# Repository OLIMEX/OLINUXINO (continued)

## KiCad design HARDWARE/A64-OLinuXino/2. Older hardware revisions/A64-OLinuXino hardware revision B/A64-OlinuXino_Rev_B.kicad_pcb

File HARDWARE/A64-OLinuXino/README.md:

## Information about the hardware schematics, design sources, and revision changes

PDF exports of the schematics are found in this folder. Deisgn files are found in the folders, each folder features all required files for a specific hardware revision as indicated by the folder name. To access the design files you need the latest beta version of KiCAD. Using the latest stable version usually will NOT suffice.

The initial release of A64-OLinuXino boards was revision C. The six variants of the board so far are:

* A64-OLinuXino-1G with 1GB RAM but NO flash and NO WiFi/BLE connectivity

* A64-OLinuXino-1Ge16GW with 1GB RAM and 16GB extra eMMC flash and extra WiFi/BLE module

* A64-OLinuXino-1Ge16GW-EA with 1GB RAM and 16GB extra eMMC flash and extra WiFi/BLE module + external antenna

* A64-OLinuXino-1Ge4GW with 1GB RAM and 4GB extra eMMC flash and extra WiFi/BLE module

* A64-OLinuXino-1Gs16M with 1GB RAM, no NAND or eMMC flash, no WiFi/BLE, extra 16MB SPI flash

* A64-OLinuXino-2Ge8G-IND with 2GB RAM and 8GB extra flash but NO WiFi/BLE connectivity; with components that work in the industrial -40+85C temperature range

### Hardware revision changes log:

#### Hardware revision C

* initial release

#### Hardware revision D

* 1. Adjusted white print of label C184.
* 2. Added bypass R66 NA(0R) near FET2.
* 3. Added white print for the UART connector at the bottom of the board (Tx,Rx,GND).
* 4. Fixed white print of R106 and R116 (labels were swapped)
* 5. R29 placed a bit further from C84
* 6. 1.5v test pad name was changed to "DDR-VCC" because the RAM memory can work at 1.3V.
* 7. Names of the jumpers lineinr/micin1p1 and lineinl/micin1n1 were changed to lineinr/micin1 and lineinl/micin2.
* 8. The jumper phoneoutr(l)/lineootr(l) was renamed to hphoneoutr(l)/lineoutr(l).

#### Hardware revision E

* 1. Changed the eMMC from eMMC (4GB,1.00mm pitch) to eMMC (16GB,0.50mm pitch). Some of the surrounding components changed too.
** 1.1 Removed RM1(RA1206_(4X0603)_4B8_10k), RM2(RA0805_(4X0402)_22R), RM3(RA0805_(4X0402)_22R), RM4(RA1206_(4X0603)_4B8_10k), RM5(RA0805_(4X0402)_22R)
* 2. C212 and C213 were changed from 27pF to 33pF and from 0603 to 0402 as component optimisation.
* 3. R66 value changed from NA(0R) to NA(22R)
* 4. RM15's package changed from RA1206_(4X0603)_4B8_22R to RA0805_(4X0402)_22R as component optimisation.
* 5. C119 and VR1 changed from PTH to SMT type in the KiCad settings. In reallity, C119 and VR1 did not change. 
* 6. PWRLED1 and CHGLED1 labels corrected in the white print.
* 7. WP_Enable1 jumper added to the SPI_Flash.
* 8. U4 changed from NA(H27UBG8T2BTR-BC(TSOP48)) to NA(MT29F64G08CBABA-WP(TSOP48)), i.e. when populated 8GB NAND instead of 4GB.
* 9. MICRO_SD(TFC-WPAPR-08) package change - corrected cream layer and origin.
* 10. PWR_PC1 jumper state changed to Soldered(2-3); Opened(1-2) so that 1.8V wire is connected to the eMMC by default.
* 11. Serial resistors added to the Ethernet PHY's Tx lines for better EMI supression and RLC filters to the clock lines.
* 12. C198 connected to the right side of the RGMII_RXCLK line.
* 13. The Wi-Fi's baloun now matched with the same "Pi" - filter like in Teres-I, so:
	C105 changed from 33pF to 10pF
	C106 changed from NA to 0.8pF
	R62 was exchanged with inductor 3.3nH
	C107 was changed from NA to 1.5pF
* 14. The WiFi's antenna mirrored

#### Hardware revision E1

* 1. eMMC KLMAG2GEND-B031(FBGA153)(16G) changed with new eMMC KLMAG1JETD-B041(FBGA153)(16G)

#### Hardware revision F

* 1. Added R62(10k/0402) pull-down to the eMMC's data strobe line;
* 2. RM14, RA0805_(4X0402)_22R replaced by 4 resistors 22R/0402, i.e. R121-R124; R121 was placed away from UEXT for to make shorter eMMC's data strobe line length;
* 3. R73[NA(22R/0402)] was added to enable SPI0 software CS option to the UEXT via PH10, when the SPI_Flash is populated. By defalut, it will reamin as it was, i.e. R124(22R/0402) populated!, while R73(NA)!;
* 4. L9 was changed from 2.7nH/L0402 to NA(2.7nH/L0402), and C88 from 24pF to NA(24pF);
* 5. MIPI-DSI1 changed: MIPI-DSI1 connector's pinout completely changed for Raspberry-Pi compatability; added the resistors: R125 to R132;
* 6. In the DRC drill to drill clerance was set to 12mils and all related errors were corrected;
* 7. UEXT1 was changed from NA(HN2x5) to HN2x5;
* 8. All 3Ds were assigned;
* 9. It was added C94(NA/0402) to the eMMC's clock line just in case;
* 10. NAND and related components removed forever;
* 11. In the schematic all "/" signs were exchanged with "\";
* 12. Improvements around the placement of a number of resistors related to the PHY signals to reduce EMI emissions;
* 13. Added U4 EEPROM - AT24C16C-SSHM-T(SOIC-8_150mil) and also C39, 100nF/10V/10% to the UEXT's I2C to avoid conflict with the same EEPROM on the LCD-Driver board. It is placed by default;
* 14. R15[NA(22R/R0402)] added in serial to the eMMC's datastrobe signal to be able to disconnect when no HS400 mode or to add a serial filter to reduce EMI;
* 15. UBOOT1, PWRON1 and RESET1 packages changed from OLIMEX_Buttons-FP:uTACTIL to OLIMEX_Buttons-FP:IT1185AU2_V2;
* 16. U2 and U3's packages improved;
* 17. LAN1's package improved;
* 18. D1 moved a little bit away from the PWR-JACK's + pad;
* 19. Q2 package changed from Q32.768kHz\12.5pF/20ppm/4P/SMD8038 to Q32.768kHz/12.5pF/2P/SMD1206;
* 20. L7 package changed from 2.7nH\L0402 to NA(2.7nH\L0402), and C198 changed from 24pF to NA(24pF);
* 21. R100 changed from 22R/0402 to FB1, FB0402/PZ1005U601-R45TF-1;
* 22. R69 changed from 22R/0402 to FB2, FB0402/PZ1005U601-R45TF-1;
* 23. The GND polygons in the top and bottom opened to allow for metal cover soldering.

#### Hardware revision G

* 1. Added antenna ANT2(NA(U.FL-R-SMT-1)), R16(0R) and R17(NA/0R);
* 2. Removed FB1(FB0402/PZ1005U601-R45TF-1) and FB2(FB0402/PZ1005U601-R45TF-1) and placed R18(22R/0402) and R19(22R/0402) resistors instead. Using FB1 and FB2 was meant to improve the EMI, but it yielded no results;
* 3. Adjusted the lengths of some eMMC wires;
* 4. C93 changed from 24pF to 24pF\50V/5%. C88 and C198 changed from NA/24pF to NA(24pF\50V/5%);
* 5. Changing 5.1 eMMC at 3.3V (up from 1.8V operation) for better reliability, PWR_PC1 jumper has to be set to position 1-2 for 3.3V operation.

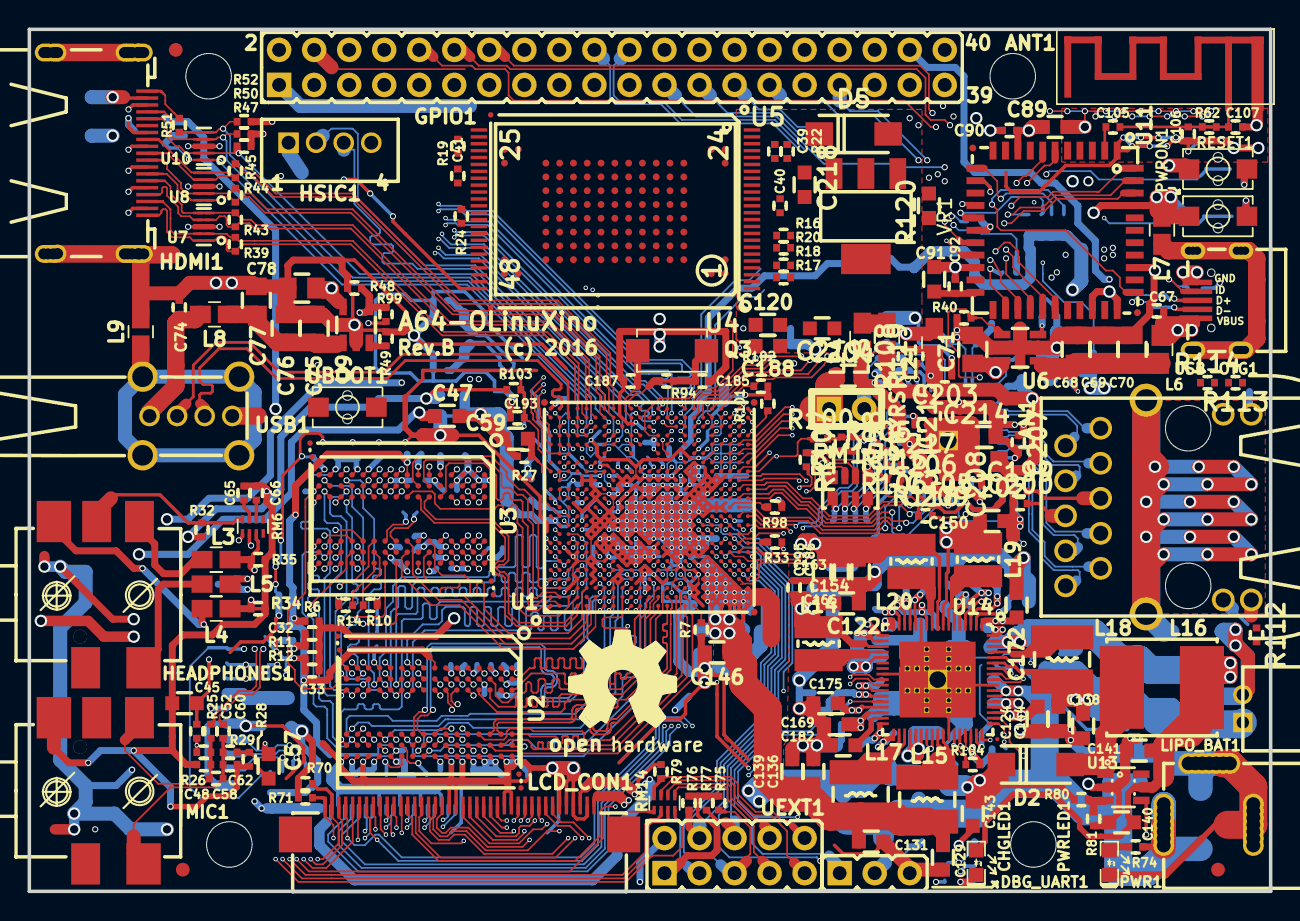
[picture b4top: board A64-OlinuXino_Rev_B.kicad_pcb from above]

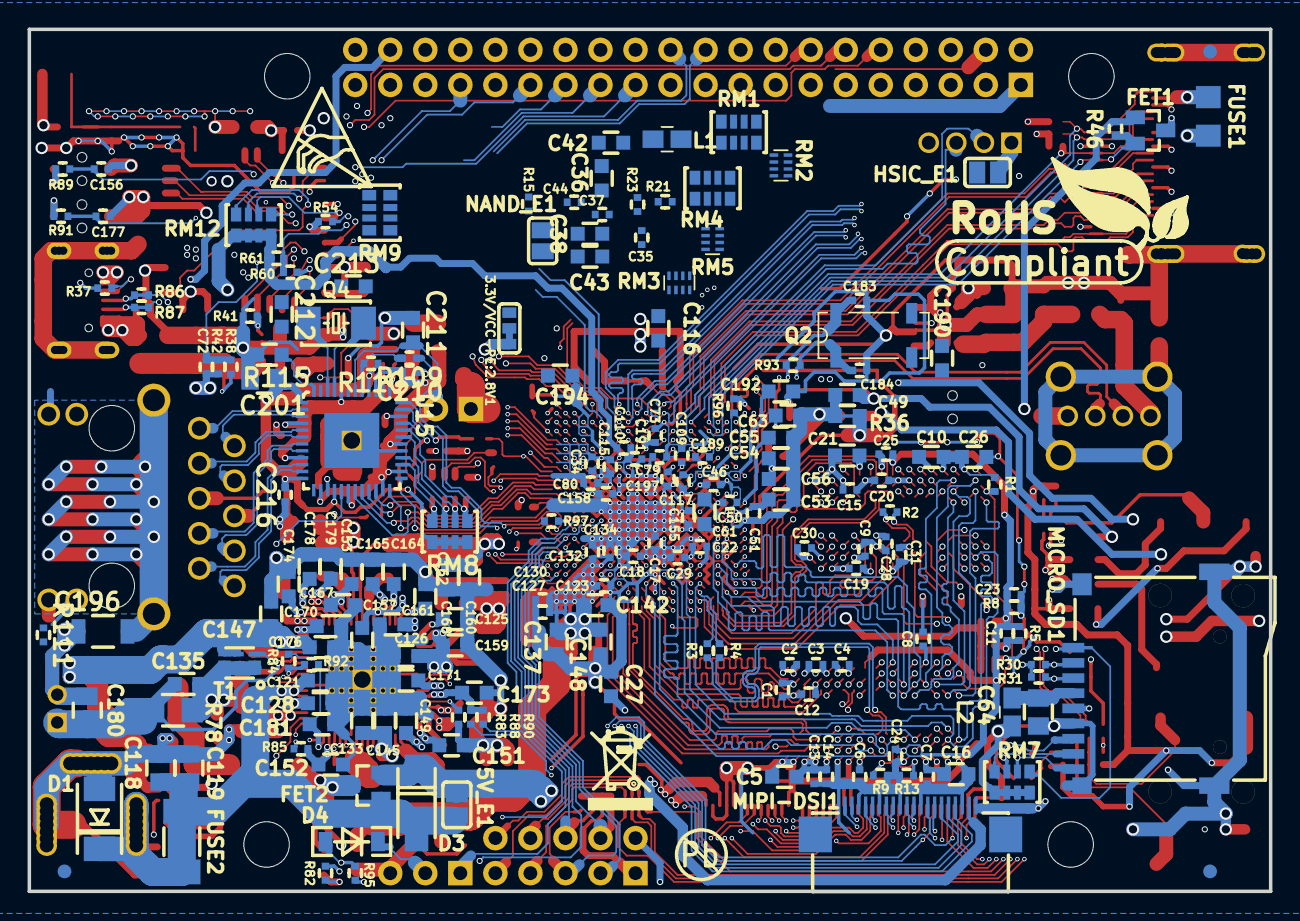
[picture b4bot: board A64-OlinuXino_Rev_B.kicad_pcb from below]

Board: 6 copper layers, 90.0 x 62.5 mm, 388 parts (188 on the bottom side), 393 nets.

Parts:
3.3V/VCC-PE:2.8V1: Opened(2-3);Closed(1-2); SJ_2_SMALL_12_TIED
5V_E1: Opened; SJ
ANT1: PCB_WIFI_ANT; bt_antenna_1ant_2gnd
C1, C2, C3, C4, C6, C7, C8, C9, C11, C12, C13, C14, C15, C17, C18, C19, C20, C22, C23, C24, C25, C28, C29, C30, C31, C32, C33, C34, C35, C37, C44, C46, C50, C51, C52, C60, C65, C66, C67, C72, C73, C74, C79, C80, C90, C92, C109, C110, C115, C117, C123, C127, C130, C132, C134, C155, C156, C158, C177, C186, C189, C191, C195, C197, C199, C200, C203, C206, C207, C208, C209, C210, C215, C216, C217: 100nF; C_0402_5MIL_DWS
C5, C10, C16, C21, C26, C42, C47, C49, C53, C54, C57, C59, C63, C89, C91, C116, C121, C122, C124, C125, C126, C128, C129, C131, C133, C136, C138, C139, C140, C141, C143, C144, C145, C146, C147, C148, C149, C150, C151, C152, C153, C154, C157, C159, C161, C162, C164, C165, C166, C167, C168, C169, C170, C171, C172, C173, C175, C176, C178, C179, C188, C192, C194: 10uF/6.3V/0603; C_0603_5MIL_DWS
C27, C36, C38, C43, C45, C55, C120, C135, C137, C142, C160, C163, C181, C182, C190: 1uF/6.3V/0603; C_0603_5MIL_DWS
C39, C40, C41: NA(100nF); C_0402_5MIL_DWS
C48, C62, C105, C185, C187: 33pF; C_0402_5MIL_DWS
C56, C61: 2.2uF/6.3V/0603; C_0603_5MIL_DWS
C58: 100pF; C_0402_5MIL_DWS
C64, C68, C69, C70, C71, C75, C76, C77, C78, C118, C119, C180, C201, C202: 47uF/6.3V/0805; C_0805_5MIL_DWS
C106, C107, C198: NA; C_0402_5MIL_DWS
C174: NA(10uF/6.3V/0603); C_0603_5MIL_DWS
C183, C184: 10pF; C_0402_5MIL_DWS
C193: NA(1nF); C_0402_5MIL_DWS
C196: 1nF/2kV/X7R/1206; C_1206_5MIL_DWS_ISO
C204, C205, C214, C218, C219: 22uF/6.3V; C_0603_5MIL_DWS
C211: NA(10uF/6.3V); C_0603_5MIL_DWS
C212, C213: 27pF; C_0603_5MIL_DWS
CHGLED1: LED/YELLOW/0603; LED_0603_KA
D1: SMBJ6.0A; DO214AA
D2, D3: 1N5822/SS34/SMA; SMA-KA
D4: 1N5819(S4SOD-123); SOD-123_1C-2A_KA
D5: 1N4007/SMA; SMA-KA
DBG_UART1: NA(HN1x3); HN1x3
FET1: BSS138(SOT23-3); SOT23
FET2: IRLML6402(SOT-23); SOT23
FUSE1: FSMD035; FUSE-1206
FUSE2: NA(5025); FUSE-5025
GPIO1: NA(HN2x20); HN2x20
HDMI1: HDMI-SWM-19
HEADPHONES1: SCJ325P00XG0B02G
HSIC1: B4B-PH-K-S
HSIC_E1: Opened; SJ
L1, L2, L3, L4, L5, L6, L7, L8, L9, L21, L23, L24: FB0805/600R/2A; L_0805_5MIL_DWS
L14, L19, L20: SWPA3015S1R5NT(1.5uH/2.30A/DCR<0.1R/CD32); CD32
L15, L17, L18: SWPA4018S1R5NT(1.5uH/3.35A/DCR<0.1R/CD43); CD42(43)
L16: 2.2uH/3A/YS75/7x8; YS75_7X8MM
LAN1: TM211Q01FM22
LCD_CON1: FPV-WZA21-40-LF
LIPO_BAT1: DW02R; LIPO_BAT-CON2DW02R
MIC1: SCJ325P00XG0B02G
MICRO_SD1: MICRO_SD(TFC-WPAPR-08); TFC-WPAPR-08
MIPI-DSI1: FPV-WZA21-20-LF
MountingHole: Mounting_hole_3.3mm
MountingHole#2, MountingHole#3, MountingHole#4: Mounting_hole_3.3mm
NAND_E1: Unsoldered; SJ
PHYRST1: HN1x2(Opened); HN1x2_Jumper
PWR1: PWRJ-2mm(YDJ-1136); PWR_JACK_UNI_MILLING
PWRLED1: LED/Red/0603; LED_0603_KA
PWRON1: IT1185AU2; uTACTIL
Q2: MC-306_32.768KHZ/SMD_8038/6pF; MC306-HS
Q3: 4SB24.000F20E15/5x3.2mm/20ppm/20pF; Q5x3.25
Q4: E4SB25.000F20E15(25MHz/20pF/20ppm/5x3.2mm); HCX-4S_2Pins_5.0x3.2mm
R1, R5, R8, R11, R12: 2k/1%; R_0402_5MIL_DWS
R2: 100R/1%; R_0402_5MIL_DWS
R3, R4, R33, R54, R100, R105, R109: 22R; R_0402_5MIL_DWS
R6, R19, R20, R24, R84, R96, R97, R98, R116, R118: NA; R_0402_5MIL_DWS
R7, R9, R10: 243R/1%; R_0402_5MIL_DWS
R13, R14: NA(243R/1%); R_0402_5MIL_DWS
R15, R16, R17, R22, R48, R61, R104: NA(10k); R_0402_5MIL_DWS
R18: NA(22R); R_0402_5MIL_DWS
R21, R23, R31, R37, R40, R42, R52, R76, R79, R83, R85, R95, R99, R106, R119: 10k; R_0402_5MIL_DWS
R25, R28, R89, R91, R92, R107, R108, R110, R111, R112, R113, R114, R117: 1k; R_0402_5MIL_DWS
R26, R29: 1.5k; R_0402_5MIL_DWS
R27: 200k/1%; R_0402_5MIL_DWS
R30, R35: 100k; R_0402_5MIL_DWS
R32: NA(1M); R_0402_5MIL_DWS
R34, R62, R86, R87, R94: 0R(Board_Mounted); R_0402_5MIL_0R(Board_Mounted)
R36: 0R(Board_Mounted); R_0603_5MIL_0R(Board_Mounted)
R38, R51: 4.7k; R_0402_5MIL_DWS
R39, R43, R44, R45: NA(510R); R_0402_5MIL_DWS
R41: 13k/1%; R_0402_5MIL_DWS
R46: 27k; R_0402_5MIL_DWS
R47, R50, R70, R71, R74, R75, R77, R82, R88, R90: 2.2k; R_0402_5MIL_DWS
R49: 3.92k/1%; R_0402_5MIL_DWS
R60: NA(0R); R_0402_5MIL_DWS
R78: 0.01R/1%/1206; R_1206_5MIL_DWS
R80: 8.25k/1%; R_0402_5MIL_DWS
R81: 1.1k/1%; R_0402_5MIL_DWS
R93: 10M; R_0402_5MIL_DWS
R101, R102: NA(2.2k); R_0402_5MIL_DWS
R103: NA(100k); R_0402_5MIL_DWS
R115: 12.1k/1%; R_0603_5MIL_DWS
R120: 120R; R_0603_5MIL_DWS
RESET1: IT1185AU2; uTACTIL
RM1, RM4: RA1206_(4X0603)_4B8_10k; RA1206_(4X0603)_4B8_xx
RM2, RM3, RM5, RM6, RM14: RA0805_(4X0402)_22R; RA0805_(4X0402)_xx
RM7, RM9, RM12: RA1206_(4x0603)_4B8_100k; RA1206_(4X0603)_4B8_xx
RM8: RA1206_(4x0603)_4B8_4.7k; RA1206_(4X0603)_4B8_xx
RM15: RA1206_(4x0603)_4B8_22R; RA1206_(4X0603)_4B8_xx
T1: WPM1481(DFN2X2-6L); DFN2x2-6L
U1: AllWinner-A64(FBGA396); FBGA396
U2, U3: K4B4G1646Q-HYK0(FBGA-96_256Mx16_DDR3-1600_11-11-1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; FBGA96(HYNIX_SAMSUNG_512MX16_DDR3)
U4: NA(H27UBG8T2BTR-BC(TSOP48)); TSOP48
U5: MTFC4GACAANA-4M_IT(TBGA100); TBGA100
U6, U9: SY6280AAC(SOT23-5); SOT-23-5
U7, U8, U10: NA(RCLAMP0524P(SLP2510P8)); SLP2510P8
U11: RTL8723BS(ComboModule); RL-SM02BD(RTL8723BS)
U13: MT3608(SOT23-6); SOT23-6
U14: AXP803(QFN68_8x8mm); QFN68
U15: KSZ9031RNXCC(QFN48_1DRILL(PADPITCH-0.5MM)); QFN48_1DRILL(PADPITCH-0.5MM)
UBOOT1: IT1185AU2; uTACTIL
UEXT1: NA(HN2x5); HN2x5
USB1: USB_A_VERTICAL; USB_A_VERTICAL_PTH
USB-OTG1: MICRO_USB/MISB-SWMM-5AB_LF; USB-MICRO_MISB-SWMM-5B_LF
VR1: AMS1117; SOT223

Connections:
1.1V_CPUS: C117.2, C120.2, C179.2, U1.H15, U14.5
1.1V_CPUX: C123.2, C127.2, C129.2, C130.2, C131.2, C132.2, C134.2, C136.2, C137.2, C139.2, C142.2, C146.2, C148.2, L15.2, L17.2, U1.AA1, U1.AA3, U1.AB2, U1.AC1, U1.AC2, U1.U6, U1.V2, U1.V3, U1.V4, U1.V5, U1.V6, U1.W1, U1.W3, U1.W4, U1.W5, U1.Y2, U1.Y3, U1.Y4
1.1V_SYS: C154.2, C155.2, C158.2, C160.2, C163.2, C166.2, C168.2, L20.2, U1.J12, U1.J13, U1.K14, U1.L13, U1.L14, U1.M13, U1.M14, U1.N14, U1.P14, U1.R13, U1.R14, U1.T15, U14.9
1.2V_HSIC: C178.2, C197.1, HSIC_E1.1, U1.K16, U14.3
3.0V_RTC: C152.1, C189.2, C190.2, R85.2, R104.1, U1.H16, U14.49
+1.5V: C1.1, C2.1, C3.1, C4.1, C5.1, C6.1, C7.1, C8.1, C9.1, C10.1, C11.1, C12.1, C13.1, C14.1, C15.1, C16.1, C17.1, C18.1, C19.1, C20.1, C21.1, C26.1, C27.1, C28.1, C29.1, C30.1, C31.1, C32.2, C150.2, L19.2, R1.2, R5.2, R11.2, U1.G7, U1.G8, U1.G9, U1.J8, U1.K6, U1.K7, U1.L6, U1.L7, U1.L8, U1.N7, U1.N8, U2.A1, U2.A8, U2.B2, U2.C1, U2.C9, U2.D2, U2.D9, U2.E9, U2.F1, U2.G7, U2.H2, U2.H9, U2.K2, U2.K8, U2.N1, U2.N9, U2.R1, U2.R9, U3.A1, U3.A8, U3.B2, U3.C1, U3.C9, U3.D2, U3.D9, U3.E9, U3.F1, U3.G7, U3.H2, U3.H9, U3.K2, U3.K8, U3.N1, U3.N9, U3.R1, U3.R9, U14.8
+1V8: C47.2, C50.2, C170.2, U1.E13, U14.68
+3.0VA: C46.1, C49.1, C175.1, C191.2, R32.2, R103.1, U1.G14, U1.N16, U14.31
+3.3VD: C79.2, C161.2, FET1.1, R46.1, U1.M16, U14.17
+3.3VWiFiIO: C91.2, C92.2, C110.2, C165.2, R61.2, RM9.1.1, RM9.2.1, RM9.3.1, RM9.4.1, RM12.1.1, RM12.2.1, RM12.3.1, RM12.4.1, U1.T17, U11.22, U14.13
+3V3: 3.3V/VCC-PE:2.8V1.3, C40.1, C41.1, C73.2, C80.1, C89.2, C90.2, C115.2, C116.2, C122.2, C186.2, C195.2, D5.2, GPIO1.3, L1.1, L2.1, L14.2, L21.2, LCD_CON1.3, R15.2, R16.2, R17.2, R19.2, R22.2, R24.1, R30.2, R31.2, R37.2, R70.2, R71.2, R75.1, R76.1, R77.1, R79.1, R95.2, R99.1, RM7.1.1, RM7.2.1, RM7.3.1, RM7.4.1, U1.L16, U1.N18, U1.N19, U1.T14, U1.U15, U1.U16, U4.1, U4.12, U4.24, U4.34, U4.37, U4.39, U11.9, U13.4, U14.20, UEXT1.1
+5V: 5V_E1.2, C71.1, C78.1, D3.1, FET2.2, FUSE1.1, GPIO1.1, LCD_CON1.1, MIPI-DSI1.1, R47.1, R50.1, U6.5, U9.5
+5V_EXT: 5V_E1.1, C118.2, C119.2, C121.1, D1.C, D3.2, FET2.1, FUSE2.1, FUSE2.2, PWR1.+, R74.1, U14.57, U14.58
+5V_USBOTG: C67.1, C124.1, L6.2, U14.54, USB-OTG1.1
/NAND Flash , eMMC, T-Card and Audio/HP-DET: RM6.1.1, U1.D11
/NAND Flash , eMMC, T-Card and Audio/HPOUTFB: L4.1, R34.2, U1.C10
/NAND Flash , eMMC, T-Card and Audio/HPOUTL: L5.1, RM6.2.1, U1.C13
/NAND Flash , eMMC, T-Card and Audio/HPOUTR: L3.1, R35.2, RM6.3.1, U1.C12
/NAND Flash , eMMC, T-Card and Audio/MBIAS: C45.2, R25.2, U1.E14
/NAND Flash , eMMC, T-Card and Audio/MICIN1N: C60.2, U1.B16
/NAND Flash , eMMC, T-Card and Audio/MICIN1P: C52.2, U1.B15
/NAND Flash , eMMC, T-Card and Audio/NAND0-DQ0/SDC2-D0: RM2.1.1, U1.M21, U4.29
/NAND Flash , eMMC, T-Card and Audio/NAND0-DQ1/SDC2-D1: RM2.2.1, U1.L19, U4.30
/NAND Flash , eMMC, T-Card and Audio/NAND0-DQ2/SDC2-D2: RM2.3.1, U1.K20, U4.31
/NAND Flash , eMMC, T-Card and Audio/NAND0-DQ3/SDC2-D3: RM2.4.1, U1.H20, U4.32
/NAND Flash , eMMC, T-Card and Audio/NAND0-DQ4/SDC2-D4: RM3.4.1, U1.P18, U4.41
/NAND Flash , eMMC, T-Card and Audio/NAND0-DQ5/SDC2-D5: RM3.2.1, U1.L20, U4.42
/NAND Flash , eMMC, T-Card and Audio/NAND0-DQ6/SDC2-D6: RM3.3.1, U1.J21, U4.43
/NAND Flash , eMMC, T-Card and Audio/NAND0-DQ7/SDC2-D7: RM3.1.1, U1.R21, U4.44
/NAND Flash , eMMC, T-Card and Audio/NAND0-DQS/SDC2-RST: RM5.2.1, U1.N20, U4.35
/NAND Flash , eMMC, T-Card and Audio/NAND0-RB0/SDC2-CMD: R16.1, R20.1, RM5.4.1, U1.K19, U4.7
/NAND Flash , eMMC, T-Card and Audio/NAND0-RE/SDC2-CLK: RM5.3.1, U1.G20, U4.8
/NAND Flash , eMMC, T-Card and Audio/SDC0-CLK: R33.2, U1.AC8
/NAND Flash , eMMC, T-Card and Audio/SDC0-CMD: MICRO_SD1.3, R31.1, U1.W9
/NAND Flash , eMMC, T-Card and Audio/SDC0-D0: MICRO_SD1.7, RM7.1.2, U1.W13
/NAND Flash , eMMC, T-Card and Audio/SDC0-D1: MICRO_SD1.8, RM7.2.2, U1.AB10
/NAND Flash , eMMC, T-Card and Audio/SDC0-D2: MICRO_SD1.1, RM7.4.2, U1.AB9
/NAND Flash , eMMC, T-Card and Audio/SDC0-D3: MICRO_SD1.2, R30.1, U1.AB6
/NAND Flash , eMMC, T-Card and Audio/SDC0-DET#: MICRO_SD1.9, RM7.3.2, U1.AB8
/Power Supply, Extensions and MiPi-DSI/1.8V_DVDD-CSI: C172.2, GPIO1.36, U14.1
/Power Supply, Extensions and MiPi-DSI/2.8V_AVDD-CSI: C164.2, GPIO1.38, U14.14
/Power Supply, Extensions and MiPi-DSI/3.3V_MIPI: C162.2, MIPI-DSI1.2, U14.16
/Power Supply, Extensions and MiPi-DSI/DC5SET: R84.2, R92.1, U14.62
/Power Supply, Extensions and MiPi-DSI/DSI-CKN: MIPI-DSI1.19, U1.P23
/Power Supply, Extensions and MiPi-DSI/DSI-CKP: MIPI-DSI1.20, U1.N23
/Power Supply, Extensions and MiPi-DSI/DSI-D0N: MIPI-DSI1.7, U1.T23
/Power Supply, Extensions and MiPi-DSI/DSI-D0P: MIPI-DSI1.8, U1.T22
/Power Supply, Extensions and MiPi-DSI/DSI-D1N: MIPI-DSI1.10, U1.R22
/Power Supply, Extensions and MiPi-DSI/DSI-D1P: MIPI-DSI1.11, U1.P22
/Power Supply, Extensions and MiPi-DSI/DSI-D2N: MIPI-DSI1.13, U1.N22
/Power Supply, Extensions and MiPi-DSI/DSI-D2P: MIPI-DSI1.14, U1.M22
/Power Supply, Extensions and MiPi-DSI/DSI-D3N: MIPI-DSI1.16, U1.L22
/Power Supply, Extensions and MiPi-DSI/DSI-D3P: MIPI-DSI1.17, U1.L23
/Power Supply, Extensions and MiPi-DSI/MIPI-DSI-BKL: MIPI-DSI1.6, U1.W8
/Power Supply, Extensions and MiPi-DSI/MIPI-DSI-EN: MIPI-DSI1.5, U1.Y6
/Power Supply, Extensions and MiPi-DSI/MIPI-DSI-RST: MIPI-DSI1.4, U1.AA6
/Power Supply, Extensions and MiPi-DSI/PB0: GPIO1.10, U1.V9
/Power Supply, Extensions and MiPi-DSI/PB1: GPIO1.12, U1.AB7
/Power Supply, Extensions and MiPi-DSI/PB2: GPIO1.14, U1.W10
/Power Supply, Extensions and MiPi-DSI/PB3: GPIO1.16, U1.AA7
/Power Supply, Extensions and MiPi-DSI/PB4: GPIO1.18, U1.W7
/Power Supply, Extensions and MiPi-DSI/PE0: GPIO1.5, U1.AA18
/Power Supply, Extensions and MiPi-DSI/PE1: GPIO1.7, U1.AB23
/Power Supply, Extensions and MiPi-DSI/PE2: GPIO1.9, U1.AA22
/Power Supply, Extensions and MiPi-DSI/PE3: GPIO1.11, U1.AA21
/Power Supply, Extensions and MiPi-DSI/PE4: GPIO1.13, U1.AA19
/Power Supply, Extensions and MiPi-DSI/PE5: GPIO1.15, U1.W17
/Power Supply, Extensions and MiPi-DSI/PE6: GPIO1.17, U1.W20
/Power Supply, Extensions and MiPi-DSI/PE7: GPIO1.19, U1.Y19
/Power Supply, Extensions and MiPi-DSI/PE8: GPIO1.21, U1.AC22
/Power Supply, Extensions and MiPi-DSI/PE9: GPIO1.23, U1.Y17
/Power Supply, Extensions and MiPi-DSI/PE10: GPIO1.25, U1.AB22
/Power Supply, Extensions and MiPi-DSI/PE11: GPIO1.27, U1.W21
/Power Supply, Extensions and MiPi-DSI/PE12: GPIO1.29, U1.AB20
/Power Supply, Extensions and MiPi-DSI/PE13: GPIO1.31, U1.Y22
/Power Supply, Extensions and MiPi-DSI/PE14: GPIO1.33, R101.1, U1.AC20
/Power Supply, Extensions and MiPi-DSI/PE15: GPIO1.35, R102.1, U1.Y23
/Power Supply, Extensions and MiPi-DSI/PE16: GPIO1.37, U1.AB21
/Power Supply, Extensions and MiPi-DSI/PE17: GPIO1.39, U1.W22
/S0SA0: U1.P5, U2.N3, U3.N3
/S0SA1: U1.R4, U2.P7, U3.P7
/S0SA2: U1.N5, U2.P3, U3.P3
/S0SA3: U1.N6, U2.N2, U3.N2
/S0SA4: U1.P6, U2.P8, U3.P8
/S0SA5: U1.G4, U2.P2, U3.P2
/S0SA6: U1.F3, U2.R8, U3.R8
/S0SA7: U1.E4, U2.R2, U3.R2
/S0SA8: U1.D3, U2.T8, U3.T8
/S0SA9: U1.C4, U2.R3, U3.R3
/S0SA10: U1.M4, U2.L7, U3.L7
/S0SA11: U1.U4, U2.R7, U3.R7
/S0SA12: U1.K5, U2.N7, U3.N7
/S0SA13: U1.E8, U2.T3, U3.T3
/S0SA14: U1.K4, U2.T7, U3.T7
/S0SA15: U1.T4, U2.M7, U3.M7
/S0SBA0: U1.D8, U2.M2, U3.M2
/S0SBA1: U1.R3, U2.N8, U3.N8
/S0SBA2: U1.C6, U2.M3, U3.M3
/S0SCAS: U1.C9, U2.K3, U3.K3
/S0SCKE0: U1.J3, U2.K9, U3.K9
/S0SCKE1: U1.H6, U2.J9, U3.J9
/S0SCK_N: R2.1, R4.1, U2.K7, U3.K7
/S0SCK_P: R2.2, R3.1, U2.J7, U3.J7
/S0SCS0: U1.E5, U2.L2, U3.L2
/S0SCS1: U1.H5, U2.L1, U3.L1
/S0SDQ0: U1.L3, U2.F7
/S0SDQ1: U1.G1, U2.G2
/S0SDQ2: U1.H3, U2.F2
/S0SDQ3: U1.K1, U2.H7
/S0SDQ4: U1.H2, U2.E3
/S0SDQ5: U1.H1, U2.H3
/S0SDQ6: U1.L1, U2.H8
/S0SDQ7: U1.L2, U2.F8
/S0SDQ8: U1.T3, U2.A7
/S0SDQ9: U1.T2, U2.C8
/S0SDQ10: U1.T1, U2.B8
/S0SDQ11: U1.R2, U2.D7
/S0SDQ12: U1.N3, U2.A3
/S0SDQ13: U1.N2, U2.C2
/S0SDQ14: U1.N1, U2.C3
/S0SDQ15: U1.M2, U2.A2
/S0SDQ16: U1.E3, U3.F7
/S0SDQ17: U1.F2, U3.H8
/S0SDQ18: U1.E2, U3.H7
/S0SDQ19: U1.E1, U3.F8
/S0SDQ20: U1.B1, U3.H3
/S0SDQ21: U1.B2, U3.F2
/S0SDQ22: U1.A2, U3.E3
/S0SDQ23: U1.B3, U3.G2
/S0SDQ24: U1.C5, U3.A7
/S0SDQ25: U1.B4, U3.C8
/S0SDQ26: U1.A4, U3.D7
/S0SDQ27: U1.A5, U3.B8
/S0SDQ28: U1.A7, U3.A3
/S0SDQ29: U1.A8, U3.C3
/S0SDQ30: U1.B8, U3.A2
/S0SDQ31: U1.B9, U3.C2
/S0SDQM0: U1.J2, U2.E7
/S0SDQM1: U1.P3, U2.D3
/S0SDQM2: U1.C2, U3.E7
/S0SDQM3: U1.B7, U3.D3
/S0SDQS0_N: U1.K2, U2.G3
/S0SDQS0_P: U1.K3, U2.F3
/S0SDQS1_N: U1.P2, U2.B7
/S0SDQS1_P: U1.P1, U2.C7
/S0SDQS2_N: U1.D1, U3.G3
/S0SDQS2_P: U1.D2, U3.F3
/S0SDQS3_N: U1.B5, U3.B7
/S0SDQS3_P: U1.B6, U3.C7
/S0SODT0: U1.D5, U2.K1, U3.K1
/S0SODT1: U1.E7, U2.J1, U3.J1
/S0SRAS: U1.F7, U2.J3, U3.J3
/S0SRST: R1.1, U1.D10, U2.T2, U3.T2
/S0SVREF: C22.2, C32.1, C33.2, R6.2, R11.1, R12.2, U1.G5
/S0SWE: U1.C8, U2.L3, U3.L3
/USB&HDMI,WiFi&BT,Ethernet,LCD/1.25_EXT: C219.1, L23.2, L24.2, R120.1, VR1.2
/USB&HDMI,WiFi&BT,Ethernet,LCD/AP-WAKE-BT: U1.B20, U11.6
/USB&HDMI,WiFi&BT,Ethernet,LCD/BT-PCM-CLK: U1.AB18, U11.26
/USB&HDMI,WiFi&BT,Ethernet,LCD/BT-PCM-DIN: U1.AC19, U11.27
/USB&HDMI,WiFi&BT,Ethernet,LCD/BT-PCM-DOUT: U1.U22, U11.25
/USB&HDMI,WiFi&BT,Ethernet,LCD/BT-PCM-SYNC: U1.AB19, U11.28
/USB&HDMI,WiFi&BT,Ethernet,LCD/BT-RST-N: RM12.1.2, U1.A20, U11.34
/USB&HDMI,WiFi&BT,Ethernet,LCD/BT-UART-CTS: U1.AC17, U11.44
/USB&HDMI,WiFi&BT,Ethernet,LCD/BT-UART-RX: RM12.4.2, U1.AB17, U11.43
/USB&HDMI,WiFi&BT,Ethernet,LCD/BT-UART-TX: U1.U23, U11.42
/USB&HDMI,WiFi&BT,Ethernet,LCD/BT-WAKE-AP: U1.D19, U11.7
/USB&HDMI,WiFi&BT,Ethernet,LCD/EPHY-RST#: R117.2, U1.Y14
/USB&HDMI,WiFi&BT,Ethernet,LCD/GCLKIN/LCD_VSYNC: LCD_CON1.30, R109.1, U1.AC11
/USB&HDMI,WiFi&BT,Ethernet,LCD/GMDC/LCD-PWM: LCD_CON1.36, U1.Y13, U15.36
/USB&HDMI,WiFi&BT,Ethernet,LCD/GMDIO/LCD_PWR: LCD_CON1.35, R108.1, U1.AC10, U15.37
/USB&HDMI,WiFi&BT,Ethernet,LCD/GRXCK/LCD_D18: LCD_CON1.7, R100.1, U1.AC16
/USB&HDMI,WiFi&BT,Ethernet,LCD/GRXCTL/LCD_D19: LCD_CON1.8, R105.1, U1.AB16
/USB&HDMI,WiFi&BT,Ethernet,LCD/GRXD0/LCD_D15: LCD_CON1.20, RM15.1.2, U1.Y16
/USB&HDMI,WiFi&BT,Ethernet,LCD/GRXD1/LCD_D14: LCD_CON1.19, RM15.2.2, U1.W16
/USB&HDMI,WiFi&BT,Ethernet,LCD/GRXD2/LCD_D13: LCD_CON1.18, RM15.3.2, U1.AA13
/USB&HDMI,WiFi&BT,Ethernet,LCD/GRXD3/LCD_D12: LCD_CON1.17, RM15.4.2, U1.V17
/USB&HDMI,WiFi&BT,Ethernet,LCD/GTXCK/LCD_DE: LCD_CON1.32, U1.AB12, U15.24
/USB&HDMI,WiFi&BT,Ethernet,LCD/GTXCTL/LCD_HSYNC: LCD_CON1.29, U1.AB11, U15.25
/USB&HDMI,WiFi&BT,Ethernet,LCD/GTXD0/LCD_CLK: LCD_CON1.31, U1.AB13, U15.19
/USB&HDMI,WiFi&BT,Ethernet,LCD/GTXD1/LCD_D23: LCD_CON1.12, U1.AC13, U15.20
/USB&HDMI,WiFi&BT,Ethernet,LCD/GTXD2/LCD_D22: LCD_CON1.11, U1.AC14, U15.21
/USB&HDMI,WiFi&BT,Ethernet,LCD/GTXD3/LCD_D21: LCD_CON1.10, U1.AB14, U15.22
/USB&HDMI,WiFi&BT,Ethernet,LCD/HCEC: FET1.2, R46.2, U1.F21, U10.1, U10.10
/USB&HDMI,WiFi&BT,Ethernet,LCD/HHPD: R51.1, R52.1, U1.E21, U10.5, U10.6
/USB&HDMI,WiFi&BT,Ethernet,LCD/HSCL: HDMI1.15, R47.2, U1.G21, U10.2, U10.9
/USB&HDMI,WiFi&BT,Ethernet,LCD/HSDA: HDMI1.16, R50.2, U1.E20, U10.4, U10.7
/USB&HDMI,WiFi&BT,Ethernet,LCD/HTX0N: HDMI1.9, R44.1, U1.G23, U8.2, U8.9
/USB&HDMI,WiFi&BT,Ethernet,LCD/HTX0P: HDMI1.7, R44.2, U1.G22, U8.1, U8.10
/USB&HDMI,WiFi&BT,Ethernet,LCD/HTX1N: HDMI1.6, R43.2, U1.F22, U7.5, U7.6
/USB&HDMI,WiFi&BT,Ethernet,LCD/HTX1P: HDMI1.4, R43.1, U1.E23, U7.4, U7.7
/USB&HDMI,WiFi&BT,Ethernet,LCD/HTX2N: HDMI1.3, R39.1, U1.E22, U7.2, U7.9
/USB&HDMI,WiFi&BT,Ethernet,LCD/HTX2P: HDMI1.1, R39.2, U1.D23, U7.1, U7.10
/USB&HDMI,WiFi&BT,Ethernet,LCD/HTXCN: HDMI1.12, R45.2, U1.H23, U8.5, U8.6
/USB&HDMI,WiFi&BT,Ethernet,LCD/HTXCP: HDMI1.10, R45.1, U1.H22, U8.4, U8.7
/USB&HDMI,WiFi&BT,Ethernet,LCD/LCD_D2: LCD_CON1.23, U1.AA20
/USB&HDMI,WiFi&BT,Ethernet,LCD/LCD_D3: LCD_CON1.24, U1.AA17
/USB&HDMI,WiFi&BT,Ethernet,LCD/LCD_D4: LCD_CON1.25, U1.W19
/USB&HDMI,WiFi&BT,Ethernet,LCD/LCD_D5: LCD_CON1.26, U1.AA14
/USB&HDMI,WiFi&BT,Ethernet,LCD/LCD_D6: LCD_CON1.27, U1.V18
/USB&HDMI,WiFi&BT,Ethernet,LCD/LCD_D7: LCD_CON1.28, U1.AA15
/USB&HDMI,WiFi&BT,Ethernet,LCD/LCD_D10: LCD_CON1.15, U1.Y11
/USB&HDMI,WiFi&BT,Ethernet,LCD/LCD_D11: LCD_CON1.16, U1.AA16
/USB&HDMI,WiFi&BT,Ethernet,LCD/LCD_D20: LCD_CON1.9, U1.AB15
/USB&HDMI,WiFi&BT,Ethernet,LCD/MDI[0]+: LAN1.1, U15.2
/USB&HDMI,WiFi&BT,Ethernet,LCD/MDI[0]-: LAN1.2, U15.3
/USB&HDMI,WiFi&BT,Ethernet,LCD/MDI[1]+: LAN1.3, U15.5
/USB&HDMI,WiFi&BT,Ethernet,LCD/MDI[1]-: LAN1.4, U15.6
/USB&HDMI,WiFi&BT,Ethernet,LCD/MDI[2]+: LAN1.7, U15.7
/USB&HDMI,WiFi&BT,Ethernet,LCD/MDI[2]-: LAN1.8, U15.8
/USB&HDMI,WiFi&BT,Ethernet,LCD/MDI[3]+: LAN1.9, U15.10
/USB&HDMI,WiFi&BT,Ethernet,LCD/MDI[3]-: LAN1.10, U15.11
/USB&HDMI,WiFi&BT,Ethernet,LCD/PH7/CTP-INT: LCD_CON1.37, U1.AC5
/USB&HDMI,WiFi&BT,Ethernet,LCD/PH8/CTP-RST: LCD_CON1.38, U1.Y10
/USB&HDMI,WiFi&BT,Ethernet,LCD/PHYAD0: LAN1.14, R112.1
/USB&HDMI,WiFi&BT,Ethernet,LCD/PHYAD1: LAN1.12, R113.1
/USB&HDMI,WiFi&BT,Ethernet,LCD/USB0-ID: R37.1, U1.AA8, USB-OTG1.4
/USB&HDMI,WiFi&BT,Ethernet,LCD/USB0-VBUSDET: C72.2, R38.1, R42.2, U1.AB4
/USB&HDMI,WiFi&BT,Ethernet,LCD/USB1-DM: U1.C22, USB1.2
/USB&HDMI,WiFi&BT,Ethernet,LCD/USB1-DP: U1.B23, USB1.3
/USB&HDMI,WiFi&BT,Ethernet,LCD/VDD33: C201.1, C202.1, C203.2, C216.2, C217.2, L21.1, LAN1.11, LAN1.13, R106.1, R108.2, R110.1, R111.1, R116.2, R119.2, RM8.1.2, RM8.2.2, RM8.3.2, RM8.4.2, U15.1, U15.12, U15.16, U15.34, U15.40
/USB&HDMI,WiFi&BT,Ethernet,LCD/WL-PMU-EN: RM12.2.2, U1.A19, U11.12
/USB&HDMI,WiFi&BT,Ethernet,LCD/WL-SDIO-CLK: R54.2, U1.V21
/USB&HDMI,WiFi&BT,Ethernet,LCD/WL-SDIO-CMD: RM12.3.2, U1.U20, U11.16
/USB&HDMI,WiFi&BT,Ethernet,LCD/WL-SDIO-D0: RM9.3.2, U1.U19, U11.18
/USB&HDMI,WiFi&BT,Ethernet,LCD/WL-SDIO-D1: RM9.4.2, U1.V22, U11.19
/USB&HDMI,WiFi&BT,Ethernet,LCD/WL-SDIO-D2: RM9.1.2, U1.Y21, U11.14
/USB&HDMI,WiFi&BT,Ethernet,LCD/WL-SDIO-D3: RM9.2.2, U1.W23, U11.15
/USB&HDMI,WiFi&BT,Ethernet,LCD/WL-WAKE-AP: U1.E19, U11.13
/VREF0_DDR3: C11.2, C23.1, C24.1, C25.1, R5.1, R6.1, R8.2, U2.H1, U2.M8, U3.H1, U3.M8
AP-CK32KO: R60.2, R61.1, U1.B18
AP-NMI#: R85.1, U1.G18, U14.61
AP-RESET#: C156.2, GPIO1.4, R89.2, R104.2, R118.2, U1.E17, U14.46
GND: ANT1.2, C1.2, C2.2, C3.2, C4.2, C5.2, C6.2, C7.2, C8.2, C9.2, C10.2, C12.2, C13.2, C14.2, C15.2, C16.2, C17.2, C18.2, C19.2, C20.2, C21.2, C22.1, C23.2, C24.2, C25.2, C26.2, C27.2, C28.2, C29.2, C30.2, C31.2, C33.1, C34.1, C35.1, C36.1, C37.1, C38.1, C39.2, C40.2, C41.2, C42.2, C43.2, C44.2, C64.2, C67.2, C68.1, C69.1, C70.1, C71.2, C72.1, C73.1, C74.2, C75.1, C76.1, C77.1, C78.2, C79.1, C80.2, C89.1, C90.1, C91.1, C92.1, C106.1, C107.1, C109.2, C110.1, C115.1, C116.1, C117.1, C118.1, C119.1, C120.1, C121.2, C122.1, C123.1, C124.2, C125.1, C126.1, C127.1, C128.2, C129.1, C130.1, C131.1, C132.1, C133.1, C134.1, C136.1, C137.1, C138.2, C139.1, C140.1, C141.1, C142.1, C143.1, C144.2, C145.1, C146.1, C147.2, C148.1, C149.2, C150.1, C151.2, C152.2, C153.1, C154.1, C155.1, C156.1, C157.1, C158.1, C159.1, C160.1, C161.1, C162.1, C163.1, C164.1, C165.1, C166.1, C167.1, C168.1, C169.2, C170.1, C171.2, C172.1, C173.2, C174.1, C175.2, C176.1, C177.1, C178.1, C179.1, C180.1, C181.1, C182.1, C183.2, C184.2, C185.2, C186.1, C187.2, C188.1, C189.1, C190.1, C191.1, C192.1, C193.1, C194.1, C195.1, C196.1, C197.2, C198.2, C199.1, C200.1, C201.2, C202.2, C203.1, C204.1, C205.1, C206.1, C207.1, C208.1, C209.1, C210.1, C211.1, C212.1, C213.1, C214.1, C215.1, C216.1, C217.1, C218.2, C219.2, D1.A, DBG_UART1.3, GPIO1.2, HDMI1.2, HDMI1.5, HDMI1.8, HDMI1.11, HDMI1.17, HDMI1.SH1, HDMI1.SH2, HDMI1.SH3, HDMI1.SH4, HSIC1.4, L7.1, L9.1, LCD_CON1.2, LCD_CON1.4, LCD_CON1.5, LCD_CON1.6, LCD_CON1.13, LCD_CON1.14, LCD_CON1.21, LCD_CON1.22, LIPO_BAT1.2, MICRO_SD1.6, MICRO_SD1.10, MICRO_SD1.11, MICRO_SD1.12, MICRO_SD1.13, MIPI-DSI1.3, MIPI-DSI1.9, MIPI-DSI1.12, MIPI-DSI1.15, MIPI-DSI1.18, PHYRST1.1, PWR1.-, PWRLED1.1, PWRON1.2, R7.1, R8.1, R9.2, R10.2, R12.1, R13.2, R14.2, R36.1, R40.1, R41.1, R42.1, R48.1, R49.1, R52.2, R81.2, R83.2, R84.1, R96.2, R97.2, R98.2, R107.1, R114.1, R115.2, R120.2, RESET1.2, U1.A1, U1.A23, U1.AC23, U1.C3, U1.C7, U1.D7, U1.G6, U1.G11, U1.H4, U1.H13, U1.J9, U1.J10, U1.J11, U1.J14, U1.J15, U1.K8, U1.K9, U1.K10, U1.K11, U1.K12, U1.K13, U1.L4, U1.L5, U1.L9, U1.L10, U1.L11, U1.L12, U1.L15, U1.M3, U1.M8, U1.M9, U1.M10, U1.M11, U1.M12, U1.M15, U1.N4, U1.N9, U1.N10, U1.N11, U1.N12, U1.N13, U1.N15, U1.P7, U1.P8, U1.P9, U1.P10, U1.P11, U1.P12, U1.P13, U1.R5, U1.R6, U1.R7, U1.R8, U1.R9, U1.R10, U1.R11, U1.R12, U1.R15, U1.T8, U1.T9, U1.T10, U1.T11, U1.T12, U1.T13, U1.U2, U1.U5, U1.U7, U1.U8, U1.U9, U1.U11, U1.U12, U1.V8, U1.V14, U2.A9, U2.B1, U2.B3, U2.B9, U2.D1, U2.D8, U2.E1, U2.E2, U2.E8, U2.F9, U2.G1, U2.G8, U2.G9, U2.J2, U2.J8, U2.M1, U2.M9, U2.P1, U2.P9, U2.T1, U2.T9, U3.A9, U3.B1, U3.B3, U3.B9, U3.D1, U3.D8, U3.E1, U3.E2, U3.E8, U3.F9, U3.G1, U3.G8, U3.G9, U3.J2, U3.J8, U3.M1, U3.M9, U3.P1, U3.P9, U3.T1, U3.T9, U4.2, U4.13, U4.23, U4.25, U4.36, U4.48, U5.G2, U5.G3, U5.G4, U5.G5, U5.G6, U5.G7, U5.G8, U5.G9, U5.H2, U5.H9, U5.L3, U5.L8, U5.M4, U5.M7, U5.P2, U5.P9, U6.2, U7.3, U7.8, U8.3, U8.8, U9.2, U10.3, U10.8, U11.1, U11.20, U11.31, U11.33, U11.36, U11.41, U13.2, U14.12, U14.25, U14.45, U14.59, U14.69, U15.29, U15.49, UBOOT1.2, UEXT1.2, USB1.4, USB-OTG1.5, VR1.1
GNDA: C45.1, C46.2, C47.1, C48.1, C49.2, C50.1, C51.2, C53.2, C54.1, C55.2, C56.1, C59.2, C62.2, C63.2, C65.1, C66.1, MIC1.2, R27.2, R28.2, R34.1, R35.1, R36.2, U1.A11
IPS: C126.2, C128.1, C133.2, C140.2, C141.2, C145.2, C147.1, C153.2, C157.2, C159.2, C167.2, C169.1, C176.2, CHGLED1.2, L16.1, T1.4, T1.8, U13.5, U14.4, U14.6, U14.11, U14.15, U14.19, U14.22, U14.32, U14.38, U14.39, U14.40, U14.55, U14.56, U14.66, U14.67
KEYADC: C193.2, GPIO1.8, R103.2, U1.A16
unnamed: 3.3V/VCC-PE:2.8V1.2, C194.2, R101.2, R102.2, U1.U18
unnamed: ANT1.1, C107.2, R62.2
unnamed: C37.2, C38.2, U5.E4
unnamed: C39.1, R22.1, U4.19
unnamed: C42.1, C43.1, C44.1, L1.2, U5.F2, U5.F3, U5.F4, U5.F5, U5.F6, U5.F7, U5.F8, U5.F9
unnamed: C48.2, C52.1, C58.1, MIC1.3, R26.1
unnamed: C51.1, C53.1, U1.C11
unnamed: C54.2, C56.2, U1.F12, U1.G13
unnamed: C55.1, U1.B12
unnamed: C57.1, R28.1, R29.2
unnamed: C57.2, R25.1, R26.2
unnamed: C58.2, C60.1, C62.1, MIC1.1, R29.1
unnamed: C59.1, R27.1, U1.B11
unnamed: C61.1, U1.E11
unnamed: C61.2, U1.E10
unnamed: C63.1, U1.D13
unnamed: C64.1, L2.2, MICRO_SD1.4
unnamed: C65.2, RM6.2.2
unnamed: C66.2, RM6.3.2
unnamed: C68.2, C69.2, C70.2, L6.1, R38.2, U6.1
unnamed: C74.1, L8.2, USB1.1
unnamed: C75.2, C76.2, C77.2, L8.1, U9.1
unnamed: C105.1, U11.2
unnamed: C105.2, C106.2, R62.1
unnamed: C125.2, U14.18
unnamed: C135.1, C138.1, C144.1, L18.1, R78.1, T1.1, T1.2, T1.5, T1.6, T1.7, U14.63
unnamed: C143.2, D2.1, FET2.3, R80.1
unnamed: C149.1, U14.35
unnamed: C174.2, U14.2
unnamed: C177.2, R91.2, U14.60
unnamed: C181.2, R92.2, U14.50
unnamed: C182.2, U14.33
unnamed: C183.1, Q2.1, R93.1, U1.B19
unnamed: C184.1, Q2.2, R93.2, U1.C18
unnamed: C185.1, Q3.1, R94.2
unnamed: C187.1, Q3.2, U1.K22
unnamed: C188.2, U1.P16
unnamed: C192.2, U1.G16
unnamed: C196.2, LAN1.SH1, LAN1.SH2
unnamed: C198.1, R100.2, R107.2, U15.35
unnamed: C199.2, LAN1.5
unnamed: C200.2, LAN1.6
unnamed: C204.2, C205.2, C206.2, C208.2, C209.2, C210.2, L24.1, U15.14, U15.18, U15.23, U15.26, U15.30, U15.39
unnamed: C207.2, C214.2, C215.2, L23.1, U15.4, U15.9, U15.44
unnamed: C211.2, PHYRST1.2, R116.1, R117.1, R118.1, U15.42
unnamed: C212.2, Q4.1, U15.46
unnamed: C213.2, Q4.2, U15.45
unnamed: C218.1, D5.1, VR1.3
unnamed: CHGLED1.1, R82.2
unnamed: D2.2, L16.2, U13.1
unnamed: D4.1, DBG_UART1.2
unnamed: D4.2, R95.1, U1.Y7
unnamed: DBG_UART1.1, U1.V10
unnamed: FET1.3, HDMI1.13
unnamed: FUSE1.2, HDMI1.18
unnamed: HDMI1.19, R51.2
unnamed: HEADPHONES1.1, L5.2
unnamed: HEADPHONES1.2, L4.2
unnamed: HEADPHONES1.3, L3.2
unnamed: HEADPHONES1.4, R32.1, RM6.1.2
unnamed: HSIC1.1, HSIC_E1.2
unnamed: HSIC1.2, U1.H19
unnamed: HSIC1.3, U1.G19
unnamed: L7.2, USB-OTG1.6
unnamed: L9.2, USB1.SH
unnamed: L14.1, U14.21
unnamed: L15.1, U14.43, U14.44
unnamed: L17.1, U14.36, U14.37
unnamed: L18.2, U14.65
unnamed: L19.1, U14.7
unnamed: L20.1, U14.10
unnamed: MICRO_SD1.5, R33.1
unnamed: NAND_E1.2, R15.1, U4.9
unnamed: PWRLED1.2, R74.2
unnamed: PWRON1.1, R91.1
unnamed: R3.2, U1.G2
unnamed: R4.2, U1.G3
unnamed: R7.2, U1.U1
unnamed: R9.1, U2.L8
unnamed: R10.1, U3.L8
unnamed: R13.1, U2.L9
unnamed: R14.1, U3.L9
unnamed: R18.1, R20.2, U4.6
unnamed: R19.1, U4.28
unnamed: R21.1, RM5.4.2, U5.P5
unnamed: R23.1, RM5.2.2, U5.M5
unnamed: R24.2, U4.38
unnamed: R41.2, U6.3
unnamed: R49.2, U9.3
unnamed: R54.1, U11.17
unnamed: R60.1, U11.24
unnamed: R79.2, RM14.4.1, UEXT1.10
unnamed: R80.2, R81.1, U13.3
unnamed: R82.1, U14.53
unnamed: R83.1, U14.30
unnamed: R86.1, U14.26
unnamed: R87.1, U14.27
unnamed: R89.1, RESET1.1
unnamed: R94.1, U1.K23
unnamed: R96.1, U1.H14
unnamed: R97.1, U1.AA11
unnamed: R98.1, U1.AA12
unnamed: R105.2, R106.2, U15.33
unnamed: R109.2, R110.2, U15.41
unnamed: R111.2, R112.2, U15.17
unnamed: R113.2, R114.2, U15.15
unnamed: R115.1, U15.48
unnamed: R119.1, U15.38
unnamed: RM1.1.2, RM2.4.2, U5.N3
unnamed: RM1.2.2, RM2.3.2, U5.K3
unnamed: RM1.3.2, RM2.2.2, U5.N2
unnamed: RM1.4.2, RM2.1.2, U5.K2
unnamed: RM3.1.2, RM4.4.2, U5.K9
unnamed: RM3.2.2, RM4.3.2, U5.K8
unnamed: RM3.3.2, RM4.2.2, U5.N9
unnamed: RM3.4.2, RM4.1.2, U5.N8
unnamed: RM5.3.2, U5.P6
unnamed: RM14.1.1, UEXT1.7
unnamed: RM14.2.1, UEXT1.8
unnamed: RM14.3.1, UEXT1.9
unnamed: RM8.1.1, RM15.1.1, U15.32
unnamed: RM8.2.1, RM15.2.1, U15.31
unnamed: RM8.3.1, RM15.3.1, U15.28
unnamed: RM8.4.1, RM15.4.1, U15.27
unnamed: T1.3, U14.52
PC4: GPIO1.20, NAND_E1.1, U1.T20
PC7: GPIO1.22, R17.1, R18.2, U1.T19, U4.4, U4.5
PH10: LCD_CON1.33, U1.Y8
PH11: LCD_CON1.34, U1.AA5
PL7: GPIO1.24, U1.C19
PL8: GPIO1.26, U1.B21
PL9: GPIO1.28, U1.D20
PL10: GPIO1.30, U1.D21
PL11: GPIO1.32, U1.C20
PL12: GPIO1.34, U1.D22
PMU-SCK: R88.1, U1.D17, U14.47
PMU-SDA: R90.1, U1.C17, U14.48
SPI0_CLK: RM14.3.2, U1.P20, U4.16
SPI0_CS: RM14.4.2, U1.P19, U4.10
SPI0_MISO: RM14.1.2, U1.K18, U4.17
SPI0_MOSI: RM14.2.2, U1.T21, U4.18
TWI0-SCK: LCD_CON1.39, R70.1, U1.W11
TWI0-SDA: LCD_CON1.40, R71.1, U1.AA10
TWI1-SCK: R75.2, U1.AC4, UEXT1.5
TWI1-SDA: R77.2, U1.AA9, UEXT1.6
UART3-RX: R76.2, U1.AC7, UEXT1.4
UART3-TX: U1.AB5, UEXT1.3
UBOOT: GPIO1.6, U1.F17, UBOOT1.1
USB0-DM: R87.2, U1.B22, USB-OTG1.2
USB0-DP: R86.2, U1.A22, USB-OTG1.3
USB0-DRV: R40.2, U6.4, U14.51
USB1-DRV: R48.2, R99.2, U1.U21, U9.4
VBAT: C135.2, C180.2, LIPO_BAT1.1, R78.2, U14.64
VCC-PC: C34.2, C35.2, C36.2, C151.1, R21.2, R23.2, RM1.1.1, RM1.2.1, RM1.3.1, RM1.4.1, RM4.1.1, RM4.2.1, RM4.3.1, RM4.4.1, U1.R16, U5.H3, U5.H8, U5.L2, U5.L4, U5.L7, U5.L9, U5.P3, U5.P8, U14.34
VCC-PE: 3.3V/VCC-PE:2.8V1.1, C171.1, GPIO1.40, U14.28
VCC-PL: C109.1, C173.1, R88.2, R90.2, U1.J16, U14.29
VDDFB-CPUX: U1.T6, U14.41, U14.42
